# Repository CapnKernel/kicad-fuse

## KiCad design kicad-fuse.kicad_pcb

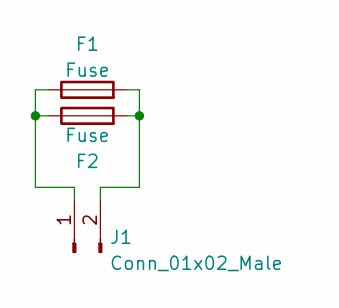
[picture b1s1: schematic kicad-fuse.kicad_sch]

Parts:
F1: Fuse; stdfuse
F2: Fuse; minifuse
J1: Conn_01x02_Male; stdfuse-pads

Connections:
unnamed: F1.1, F2.1, J1.1
unnamed: F1.2, F2.2, J1.2

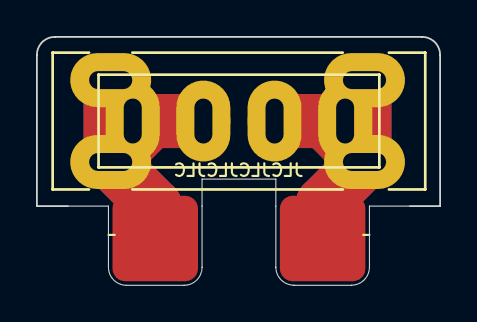
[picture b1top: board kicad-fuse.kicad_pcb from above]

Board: 2 copper layers, 22.4 x 13.8 mm, 3 parts (0 on the bottom side), 2 nets.

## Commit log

2023-05-10 Not sure.
2023-05-10 Saved files in KiCad 7.
